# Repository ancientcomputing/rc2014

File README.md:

# RC2014
I consider Spencer Owen's RC2014 (http://rc2014.co.uk) the new S100 of the ancient computing era.
<p>
Spencer started off by designing a CPU and a family of modules around the ancient Zilog Z80 CPU. This is actually very similar to the original S100 bus design that was a derivative of the 8080 bus.
<p>
Since I'm a modder at heart, I've gone ahead and modified some of the Z80 software that originally came with the RC2014.
<p>
I have also developed a number of RC2014-compatible plug-in boards. These include a variety of memory and serial (UART) boards and more importantly, boards that allow the use of other CPUs like the <a href="https://en.wikipedia.org/wiki/Intel_8085">Intel 8085</a> and <a href="https://en.wikipedia.org/wiki/MOS_Technology_6502">6502</a> with the RC2014.
<p>
This repo holds my mods/additions and general contributions to the RC2014 community.
<p>
<hr>
<p>
<b>Software</b>
<p>
The source folder contains source code of projects related to the RC2014.
<p>
The 6502 sub-folder contains all the 6502-related source code including the Monitor/Debugger and Enhanced BASIC.
<p>
The Z80_8080 sub-folder contains all source code for Z80 and 8080 software including the Monitor/Debugger, MS BASIC, IMSAI 8K BASIC (for 8080) and various BIOS.
<p>
The original code that shipped with the RC2014 is at <a href="searle.hostei.com/grant">searle.hostei.com/grant</a>
<p>
The primary RC2014 Github repo is at: https://github.com/RC2014Z80/RC2014
<p>
<hr>
<p>
<b>ROM</b>
<p>
ROM images you can burn into EPROM/EEPROM for use with the RC2014 can be found in the ROM folder.
<p>
Not all combinations of CPU, serial, Monitor/Debugger, BASIC and ROM image sizes are available. When in doubt you can ask questions on the <a href="https://groups.google.com/forum/#!forum/rc2014-z80">RC2014 group</a> or <a href="http://forum.6502.org/">http://forum.6502.org/</a>.
<p>
<hr>
<p>
<b>RC2014 Add-on Modules</b>
<p>
The <b>eagle</b> folder contain a number of designs for add-on boards for the RC2014. The designs are in the form of Eagle files which can be used to order PCBs from manufacturers that can take .brd files. Or you can download the free version of Eagle and generate the necessary gerber files for your PCB vendor of choice.
<p>
Do also watch out for the OSH Park logos. Those are links to projects that I have shared on OSH Park, and you can order the boards directly from them. And no, I don't make a commission etc from your OSH Park orders.
<p>
For a full list of my shared projects, check out this <a href="https://oshpark.com/profiles/ancientcomputing">link</a>.
<p>
I have put some popular boards up for sale on <a href="https://www.tindie.com/stores/ancientcomputing/">Tindie</a>.
<p>
<hr>
<p>
Lastly, check out the documentation in the docs folder.
<p>
<hr>
<p>
Blog: http://ancientcomputing.blogspot.com

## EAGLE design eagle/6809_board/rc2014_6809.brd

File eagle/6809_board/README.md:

<b>6809 CPU Board for the RC2014</b>
<p>
These are the EAGLE files for the RC2014 6809 CPU Board.
<p>
The A15 line selects the inverted A15 signal from the 6809. This allows you to use the standard RC2014 memory and I/O boards by inverting the 2 halves of the memory space: ROM sits at top of memory and RAM at the bottom of memory.
<p>
The I/O space is decoded by the 74HCT688 and is mapped as a 256-byte block to the start of 0C000H. You will map the Z80 I/O addresses to the 6809 I/O space by adding 0C000H.
<p>
Compatibility:
<br>TBD
<p>
You can have boards made at OSH Park at the following link:
<p>
<a href="https://www.oshpark.com/shared_projects/m4Si7sne"></img></a>
<p>

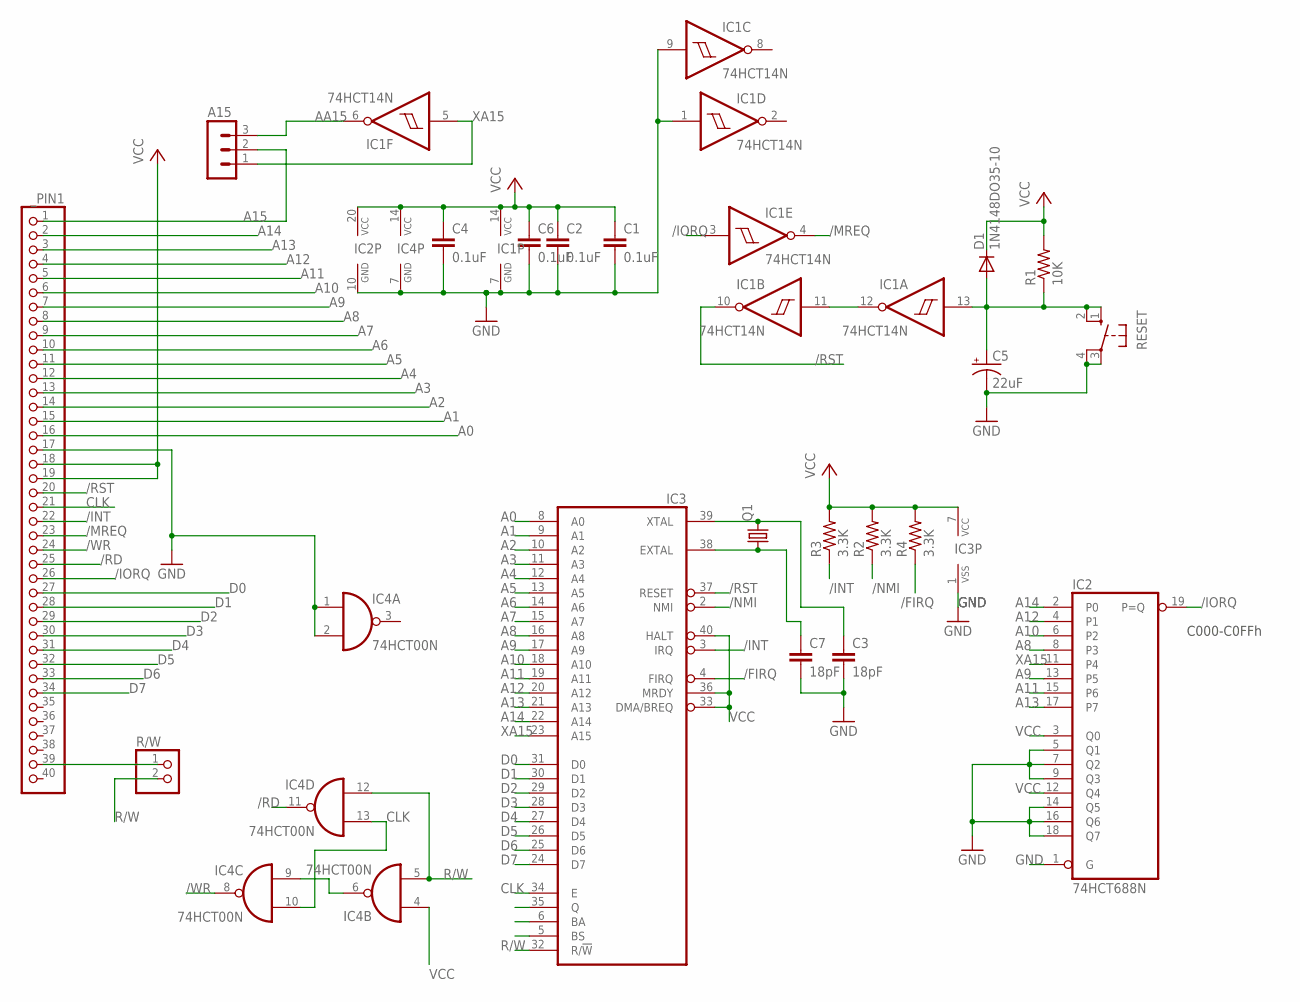
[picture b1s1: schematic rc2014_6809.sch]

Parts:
A15: MA03-1
C1, C2, C4, C6: 0.1uF; C050-024X044
C3, C7: 18pF; C050-024X044
C5: 22uF; TAP5-80
D1: 1N4148DO35-10; DO35-10
IC1: 74HCT14N; DIL14
IC2: 74HCT688N; DIL20
IC3: 6809; DIL40
IC4: 74HCT00N; DIL14
Q1: CRYSTALHC49S; HC49/S
R1: 10K; 0207/10
R2, R3, R4: 3.3K; 0207/10
R/W: PINHD-1X2; 1X02
RESET: 10-XX; B3F-10XX
_PIN1: PINHD-1X40; 1X40

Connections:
/FIRQ: IC3.4 (FIRQ), R4.1
/INT: IC3.3 (IRQ), R3.1, _PIN1.22
/IORQ: IC1.3 (I), IC2.19 (P=Q), _PIN1.26
/MREQ: IC1.4 (O), _PIN1.23
/NMI: IC3.2 (NMI), R2.1
/RD: IC4.11 (O), _PIN1.25
/RST: IC1.10 (O), IC3.37 (RESET), _PIN1.20
/WR: IC4.8 (O), _PIN1.24
A0: IC3.8 (A0), _PIN1.16
A1: IC3.9 (A1), _PIN1.15
A2: IC3.10 (A2), _PIN1.14
A3: IC3.11 (A3), _PIN1.13
A4: IC3.12 (A4), _PIN1.12
A5: IC3.13 (A5), _PIN1.11
A6: IC3.14 (A6), _PIN1.10
A7: IC3.15 (A7), _PIN1.9
A8: IC2.8 (P3), IC3.16 (A8), _PIN1.8
A9: IC2.13 (P5), IC3.17 (A9), _PIN1.7
A10: IC2.6 (P2), IC3.18 (A10), _PIN1.6
A11: IC2.15 (P6), IC3.19 (A11), _PIN1.5
A12: IC2.4 (P1), IC3.20 (A12), _PIN1.4
A13: IC2.17 (P7), IC3.21 (A13), _PIN1.3
A14: IC2.2 (P0), IC3.22 (A14), _PIN1.2
A15: A15.2, _PIN1.1
AA15: A15.3, IC1.6 (O)
CLK: IC3.34 (E), IC4.10 (I1), IC4.13 (I1), _PIN1.21
D0: IC3.31 (D0), _PIN1.27
D1: IC3.30 (D1), _PIN1.28
D2: IC3.29 (D2), _PIN1.29
D3: IC3.28 (D3), _PIN1.30
D4: IC3.27 (D4), _PIN1.31
D5: IC3.26 (D5), _PIN1.32
D6: IC3.25 (D6), _PIN1.33
D7: IC3.24 (D7), _PIN1.34
GND: C1.2, C2.2, C3.2, C4.2, C5.-, C6.2, C7.2, IC1.1 (I), IC1.7 (GND), IC1.9 (I), IC2.1 (G), IC2.5 (Q1), IC2.7 (Q2), IC2.9 (Q3), IC2.10 (GND), IC2.14 (Q5), IC2.16 (Q6), IC2.18 (Q7), IC3.1 (VSS), IC4.1 (I0), IC4.2 (I1), IC4.7 (GND), RESET.3, RESET.4 (P1), _PIN1.17
unnamed: IC4.6 (O), IC4.9 (I0)
unnamed: R/W.1, _PIN1.39
unnamed: IC1.11 (I), IC1.12 (O)
unnamed: C3.1, IC3.39 (XTAL), Q1.2
unnamed: C7.1, IC3.38 (EXTAL), Q1.1
R/W: IC3.32 (R/!W), IC4.5 (I1), IC4.12 (I0), R/W.2
RESET: C5.+, D1.A, IC1.13 (I), R1.1, RESET.1 (S), RESET.2 (S1)
VCC: C1.1, C2.1, C4.1, C6.1, D1.C, IC1.14 (VCC), IC2.3 (Q0), IC2.12 (Q4), IC2.20 (VCC), IC3.7 (VCC), IC3.33 (DMA/BREQ), IC3.36 (MRDY), IC3.40 (HALT), IC4.4 (I0), IC4.14 (VCC), R1.2, R2.2, R3.2, R4.2, _PIN1.18, _PIN1.19
XA15: A15.1, IC1.5 (I), IC2.11 (P4), IC3.23 (A15)

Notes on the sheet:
C000-C0FFh

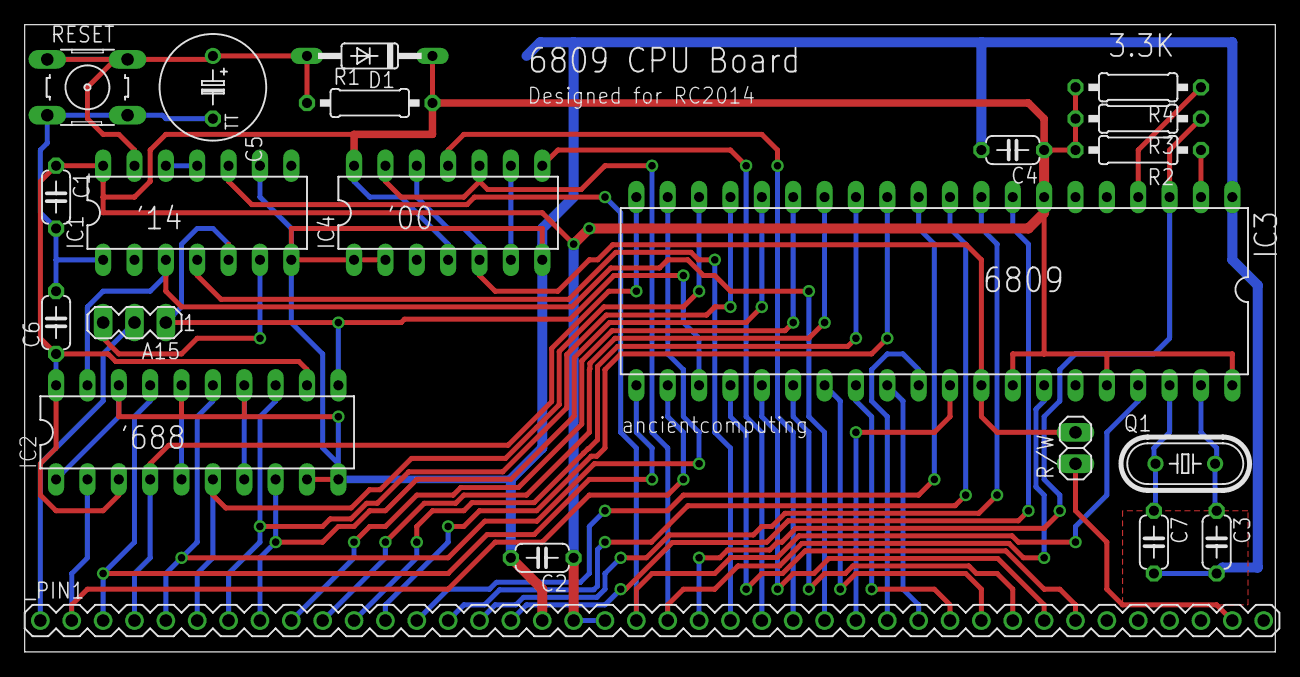
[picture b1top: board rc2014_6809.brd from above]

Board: 2 copper layers, 101.3 x 50.8 mm, 21 parts (0 on the bottom side), 44 nets.

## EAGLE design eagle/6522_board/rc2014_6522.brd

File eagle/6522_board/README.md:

<b>6522 VIA Board for the RC2014</b>
<p>
These are the Eagle files for the 6522 VIA Board for the RC2014.
<p>
The board is designed to work with the 6502 CPU Board.
<p>
If you have the initial revision (revA) of the 6502 CPU board, be sure to link a wire from the R/W signal of the 6502 to pin 39 of the RC2014 bus connector. The 6522 takes the R/W signal from that pin. RevB of the 6502 CPU board does not need that change but you want to make sure that the R/W jumper is closed.
<p>
Be sure to use a 6522 that is speed matched to the 6502 CPU.
<p>
Check out some test code <a href="https://github.com/ancientcomputing/rc2014/tree/master/source/6502/6522">here</a>.

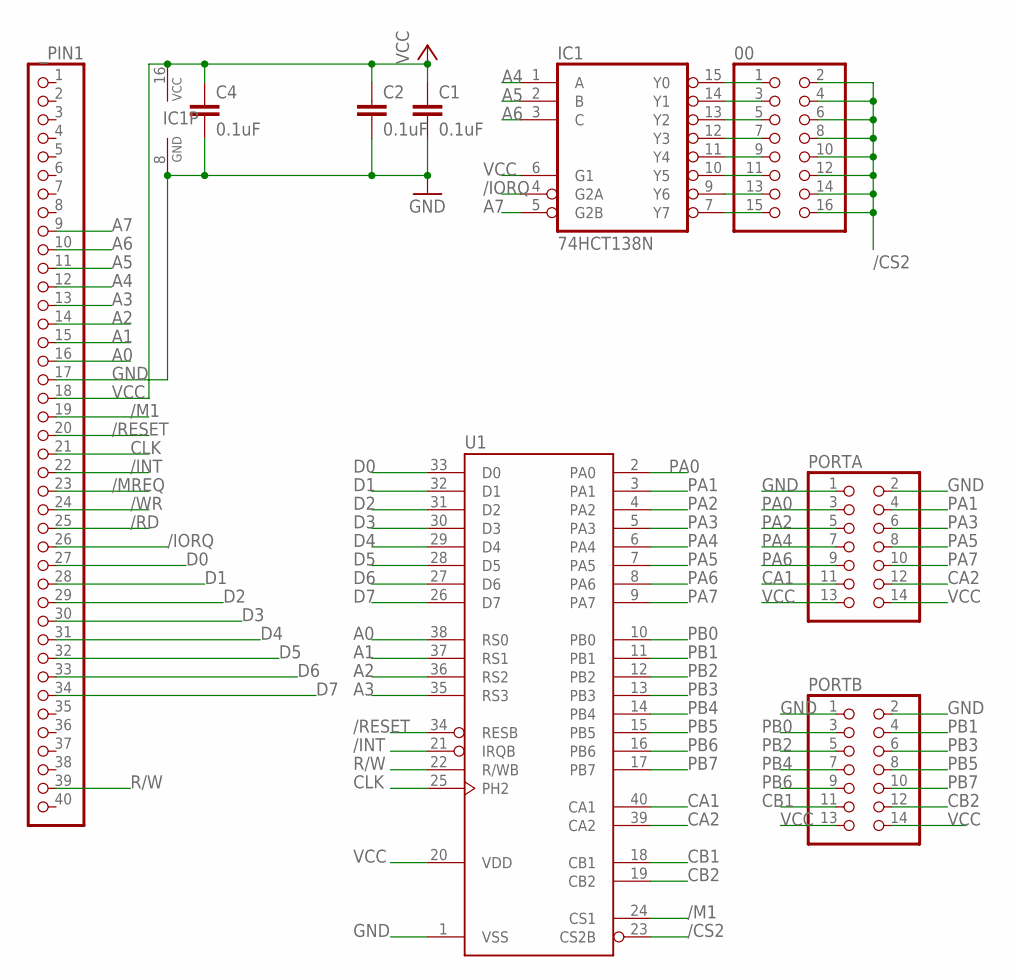
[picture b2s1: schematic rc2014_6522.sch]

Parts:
00: PINHD-2X8; 2X08
C1, C2, C4: 0.1uF; C050-024X044
IC1: 74HCT138N; DIL16
PORTA: PINHD-2X7; 2X07
PORTB: PINHD-2X7; 2X07
U1: G65SC22P; DIP-40
_PIN1: PINHD-1X40; 1X40

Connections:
/CS2: 00.2, 00.4, 00.6, 00.8, 00.10, 00.12, 00.14, 00.16, U1.23 (CS2B)
/INT: U1.21 (IRQB), _PIN1.22
/IORQ: IC1.4 (G2A), _PIN1.26
/M1: U1.24 (CS1), _PIN1.19
/MREQ: _PIN1.23
/RD: _PIN1.25
/RESET: U1.34 (RESB), _PIN1.20
/WR: _PIN1.24
A0: U1.38 (RS0), _PIN1.16
A1: U1.37 (RS1), _PIN1.15
A2: U1.36 (RS2), _PIN1.14
A3: U1.35 (RS3), _PIN1.13
A4: IC1.1 (A), _PIN1.12
A5: IC1.2 (B), _PIN1.11
A6: IC1.3 (C), _PIN1.10
A7: IC1.5 (G2B), _PIN1.9
CA1: PORTA.11, U1.40 (CA1)
CA2: PORTA.12, U1.39 (CA2)
CB1: PORTB.11, U1.18 (CB1)
CB2: PORTB.12, U1.19 (CB2)
CLK: U1.25 (PH2), _PIN1.21
D0: U1.33 (D0), _PIN1.27
D1: U1.32 (D1), _PIN1.28
D2: U1.31 (D2), _PIN1.29
D3: U1.30 (D3), _PIN1.30
D4: U1.29 (D4), _PIN1.31
D5: U1.28 (D5), _PIN1.32
D6: U1.27 (D6), _PIN1.33
D7: U1.26 (D7), _PIN1.34
GND: C1.2, C2.2, C4.2, IC1.8 (GND), PORTA.1, PORTA.2, PORTB.1, PORTB.2, U1.1 (VSS), _PIN1.17
unnamed: 00.1, IC1.15 (Y0)
unnamed: 00.3, IC1.14 (Y1)
unnamed: 00.5, IC1.13 (Y2)
unnamed: 00.7, IC1.12 (Y3)
unnamed: 00.9, IC1.11 (Y4)
unnamed: 00.11, IC1.10 (Y5)
unnamed: 00.13, IC1.9 (Y6)
unnamed: 00.15, IC1.7 (Y7)
PA0: PORTA.3, U1.2 (PA0)
PA1: PORTA.4, U1.3 (PA1)
PA2: PORTA.5, U1.4 (PA2)
PA3: PORTA.6, U1.5 (PA3)
PA4: PORTA.7, U1.6 (PA4)
PA5: PORTA.8, U1.7 (PA5)
PA6: PORTA.9, U1.8 (PA6)
PA7: PORTA.10, U1.9 (PA7)
PB0: PORTB.3, U1.10 (PB0)
PB1: PORTB.4, U1.11 (PB1)
PB2: PORTB.5, U1.12 (PB2)
PB3: PORTB.6, U1.13 (PB3)
PB4: PORTB.7, U1.14 (PB4)
PB5: PORTB.8, U1.15 (PB5)
PB6: PORTB.9, U1.16 (PB6)
PB7: PORTB.10, U1.17 (PB7)
R/W: U1.22 (R/WB), _PIN1.39
VCC: C1.1, C2.1, C4.1, IC1.6 (G1), IC1.16 (VCC), PORTA.13, PORTA.14, PORTB.13, PORTB.14, U1.20 (VDD), _PIN1.18

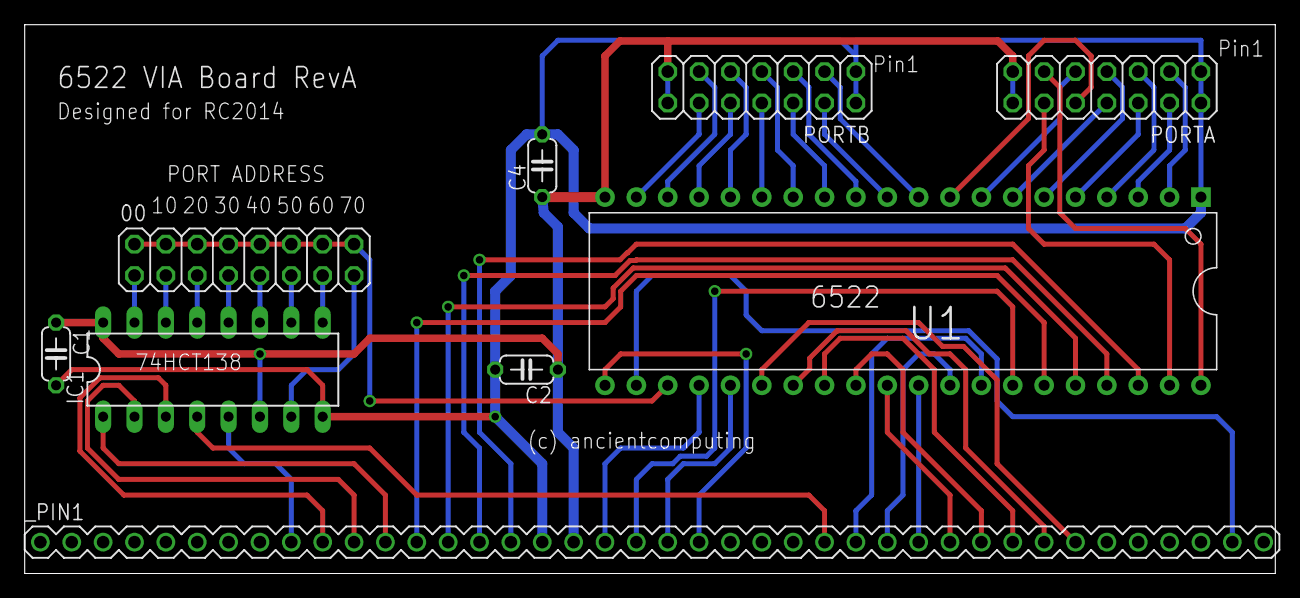
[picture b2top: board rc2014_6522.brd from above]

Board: 2 copper layers, 101.3 x 44.4 mm, 9 parts (0 on the bottom side), 53 nets.

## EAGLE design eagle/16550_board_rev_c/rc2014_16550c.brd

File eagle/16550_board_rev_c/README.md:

<b>16550 UART Board for RC2014</b>
<p>
This is RevC of the 16550 UART Board, designed for RC2014 systems.
<p>
Unlike earlier versions, this board takes the PLCC version of the 16550. I have successfully tested it with a TL16C550CFN from Mouser (part: 595-TL16C550CFN).
<p>
Also, as you can see from the Mouser part number, PLCC versions of the 16C550 are still commercially available. The DIP/DIL-40 versions are no longer so.
<p>
The use of a 16C550 in a 6502 system is important (vs the 16550 version) because the 6502 BIOS enables autoflow control. This provides a means of throttling the byte stream from your PC when you are uploading an Intel Hex file.
<p>
The other major change is the use of a 74HCT138 to give you more addressing options. This allows you to use more than one board in a system: you just need to make sure that each board uses a different port address. Of course, the software needs to be appropriately modified to access port addresses other than C0H which is the default one.
<p>
Finally, the PLCC socket is a standard part and can be ordered from Mouser (part: 806-PX-44LCC) or Jameco.
<p>
You can have boards made at OSH Park:<br>
<a href="https://www.oshpark.com/shared_projects/Rv3GdG3o"></img></a>
<p> 
Or order them on <a href="https://www.tindie.com/products/9981/">Tindie</a>.

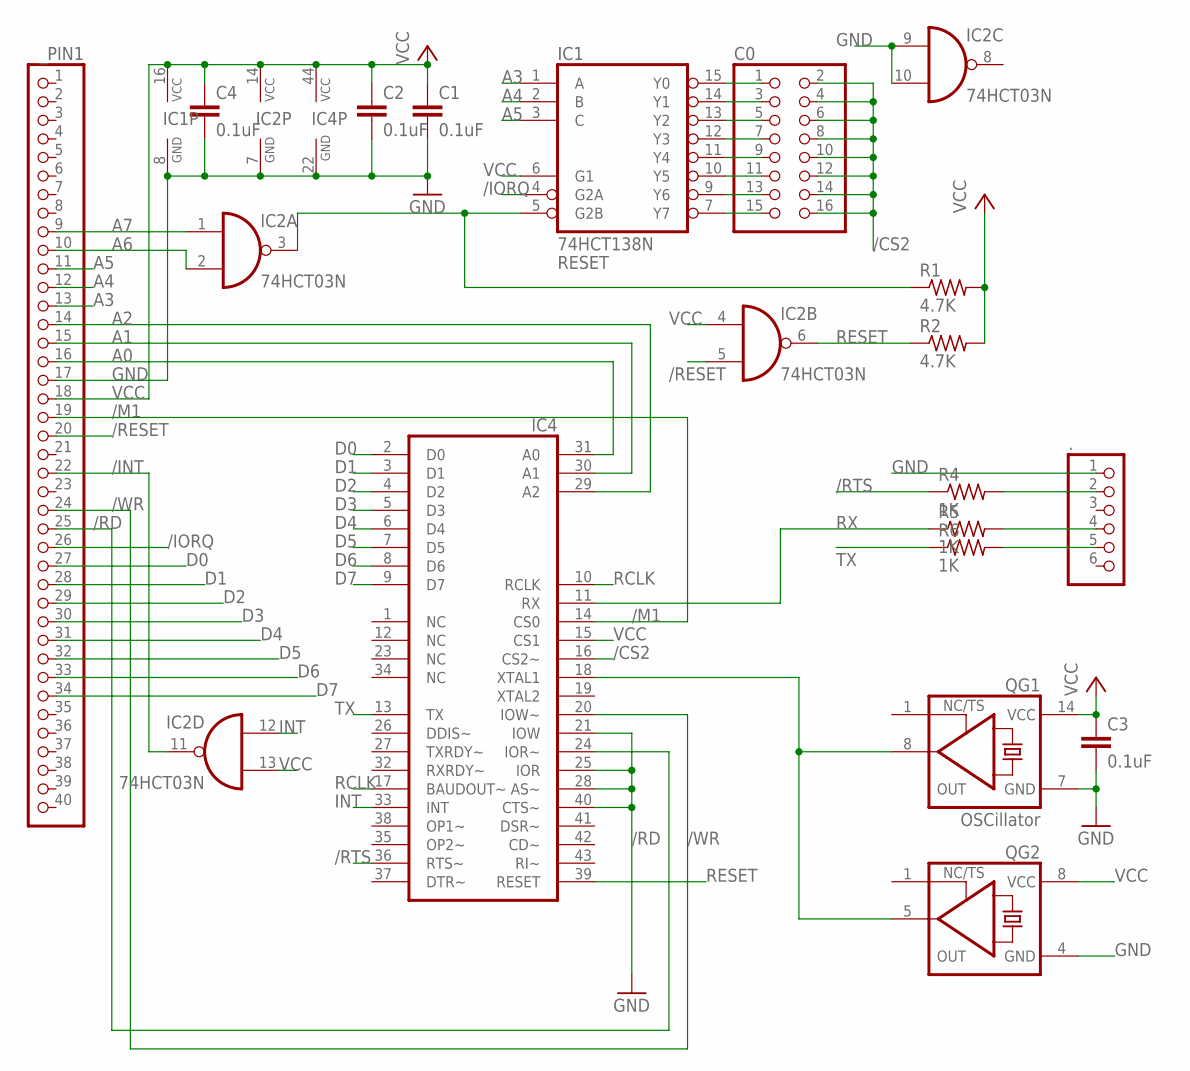
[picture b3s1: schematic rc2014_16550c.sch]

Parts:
.: PINHD-1X6; 1X06
C0: PINHD-2X8; 2X08
C1, C2, C3, C4: 0.1uF; C050-024X044
IC1: 74HCT138N; DIL16
IC2: 74HCT03N; DIL14
IC4: XR-16C550JSOCKET44; S44
QG1: OSCillator; DIL14S
QG2: XO-8; DIL08S
R1, R2: 4.7K; 0207/10
R4, R5, R6: 1K; 0207/10
_PIN1: PINHD-1X40; 1X40

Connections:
/CS2: C0.2, C0.4, C0.6, C0.8, C0.10, C0.12, C0.14, C0.16, IC4.16 (CS2~)
/INT: IC2.11 (O), _PIN1.22
/IORQ: IC1.4 (G2A), _PIN1.26
/M1: IC4.14 (CS0), _PIN1.19
/RD: IC4.24 (IOR~), _PIN1.25
/RESET: IC2.5 (I1), _PIN1.20
/RTS: IC4.36 (RTS~), R4.1
/WR: IC4.20 (IOW~), _PIN1.24
A0: IC4.31 (A0), _PIN1.16
A1: IC4.30 (A1), _PIN1.15
A2: IC4.29 (A2), _PIN1.14
A3: IC1.1 (A), _PIN1.13
A4: IC1.2 (B), _PIN1.12
A5: IC1.3 (C), _PIN1.11
A6: IC2.2 (I1), _PIN1.10
A7: IC2.1 (I0), _PIN1.9
CS1: IC1.5 (G2B), IC2.3 (O), R1.1
D0: IC4.2 (D0), _PIN1.27
D1: IC4.3 (D1), _PIN1.28
D2: IC4.4 (D2), _PIN1.29
D3: IC4.5 (D3), _PIN1.30
D4: IC4.6 (D4), _PIN1.31
D5: IC4.7 (D5), _PIN1.32
D6: IC4.8 (D6), _PIN1.33
D7: IC4.9 (D7), _PIN1.34
GND: ..1, C1.2, C2.2, C3.2, C4.2, IC1.8 (GND), IC2.7 (GND), IC2.9 (I0), IC2.10 (I1), IC4.21 (IOW), IC4.22 (GND), IC4.25 (IOR), IC4.28 (AS~), IC4.40 (CTS~), QG1.7 (GND), QG2.4 (GND), _PIN1.17
INT: IC2.12 (I0), IC4.33 (INT)
unnamed: ..5, R6.2
unnamed: ..4, R5.2
unnamed: ..2, R4.2
unnamed: C0.1, IC1.15 (Y0)
unnamed: C0.3, IC1.14 (Y1)
unnamed: C0.5, IC1.13 (Y2)
unnamed: C0.7, IC1.12 (Y3)
unnamed: C0.9, IC1.11 (Y4)
unnamed: C0.11, IC1.10 (Y5)
unnamed: C0.13, IC1.9 (Y6)
unnamed: C0.15, IC1.7 (Y7)
OSC: IC4.18 (XTAL1), QG1.8 (OUT), QG2.5 (OUT)
RCLK: IC4.10 (RCLK), IC4.17 (BAUDOUT~)
RESET: IC2.6 (O), IC4.39 (RESET), R2.1
RX: IC4.11 (RX), R5.1
TX: IC4.13 (TX), R6.1
VCC: C1.1, C2.1, C3.1, C4.1, IC1.6 (G1), IC1.16 (VCC), IC2.4 (I0), IC2.13 (I1), IC2.14 (VCC), IC4.15 (CS1), IC4.44 (VCC), QG1.14 (VCC), QG2.8 (VCC), R1.2, R2.2, _PIN1.18

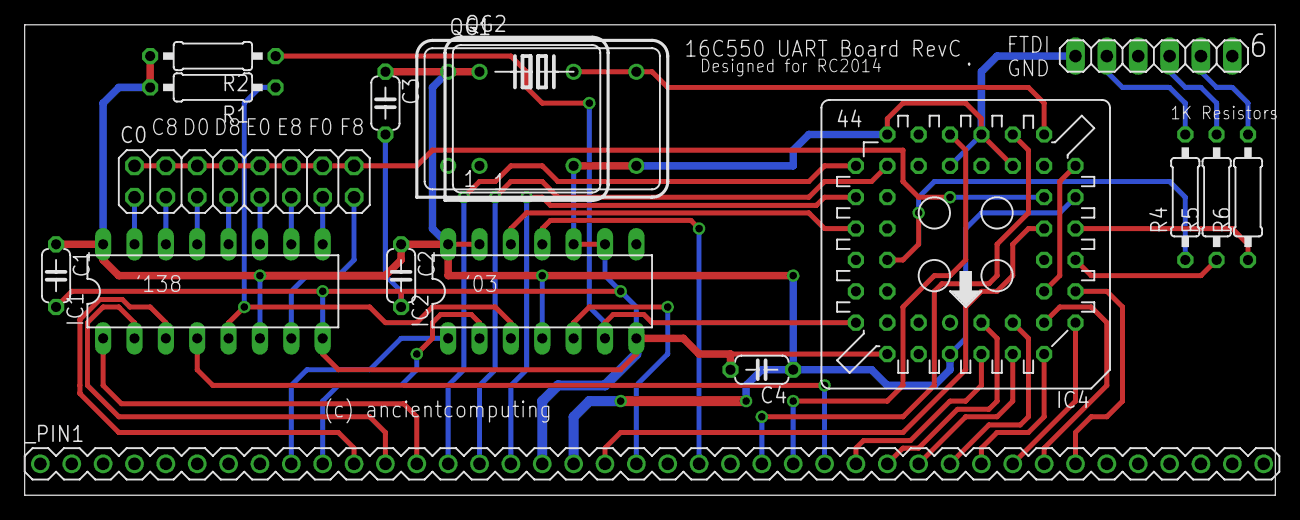
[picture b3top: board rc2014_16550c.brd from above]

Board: 2 copper layers, 101.3 x 38.1 mm, 17 parts (0 on the bottom side), 44 nets.

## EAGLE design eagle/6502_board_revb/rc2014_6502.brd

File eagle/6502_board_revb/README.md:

<b>6502 CPU Board for the RC2014 RevB</b>
<p>
This is the RevB version of the board.
<p>
New:
<br>
- Optional jumper to connect R/W to pin 39 of the bus
<br>
- A14 can be inverted. Inverting A14 will allow you to use the RC2014 64KB RAM board. Configure that board for 48KB of RAM, starting from 4000h. The inverted A14 will map the 48KB to 0-BFFFh in the 6502 address space, giving you a whopping 48KB of RAM!
<br>
- NMI can be accessed with a test pin/point
<br>
- You can use a 1/2 size oscillator.
<p>
Otherwise this board works the same as the original version.
<p>
You can have boards made at OSH Park at the following link:
<br>
<a href="https://www.oshpark.com/shared_projects/QY9iHV77"></img></a>
<p>
Otherwise, you can order boards on <a href="https://www.tindie.com/products/9916/">Tindie</a>.

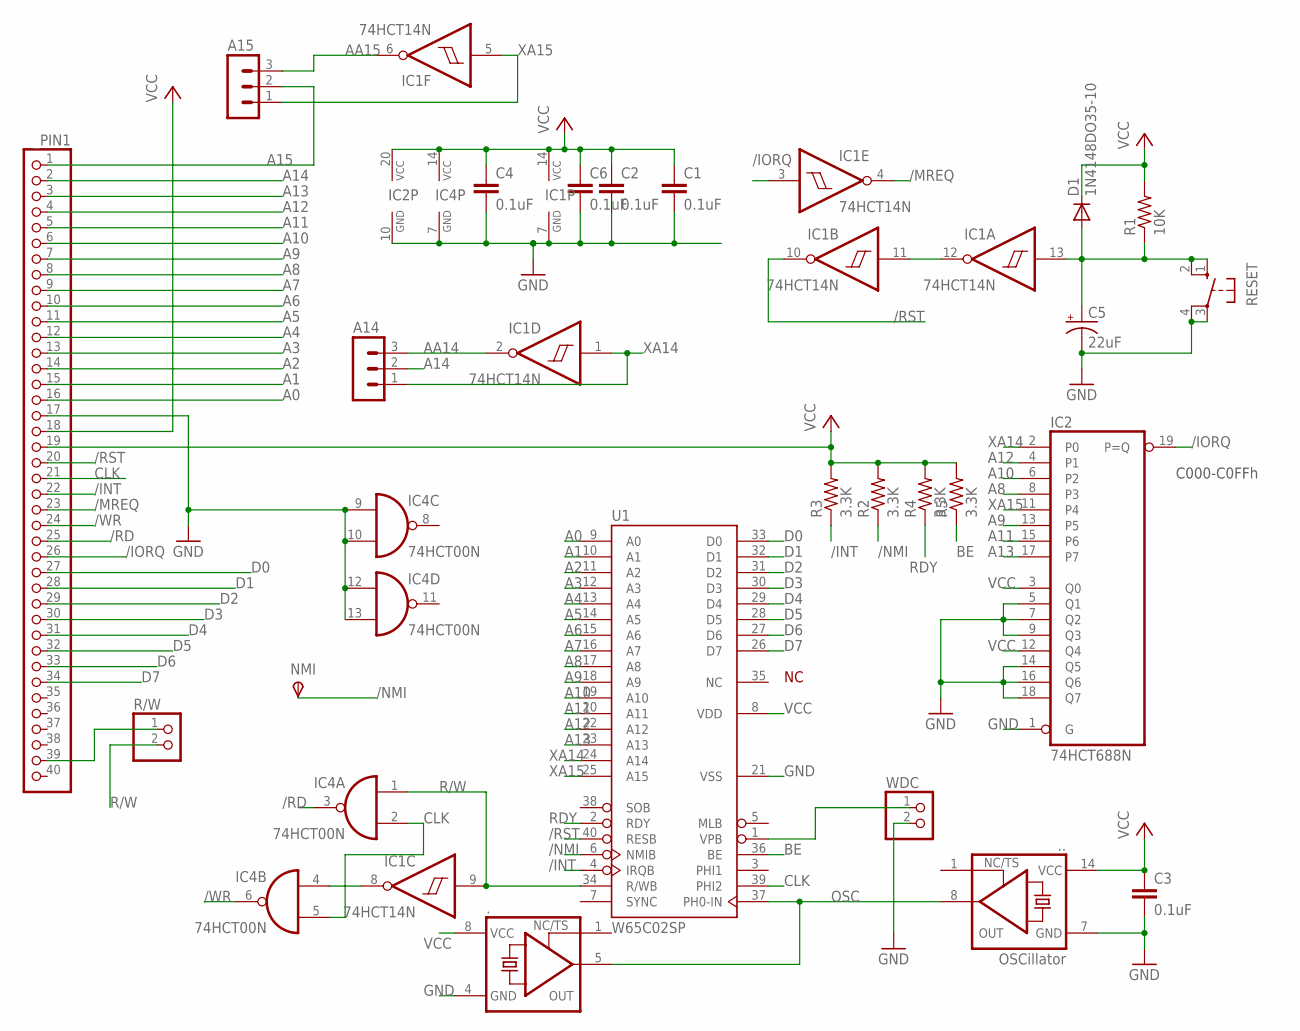
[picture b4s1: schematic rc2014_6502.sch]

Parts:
.: XO-8; DIL08S
..: OSCillator; DIL14S
A14, A15: MA03-1
C1, C2, C3, C4, C6: 0.1uF; C050-024X044
C5: 22uF; TAP5-80
D1: 1N4148DO35-10; DO35-10
IC1: 74HCT14N; DIL14
IC2: 74HCT688N; DIL20
IC4: 74HCT00N; DIL14
NMI: TPSPAD1-13; P1-13
R1: 10K; 0207/10
R2, R3, R4, R5: 3.3K; 0207/10
R/W: PINHD-1X2; 1X02
RESET: 10-XX; B3F-10XX
U1: W65C02SP; DIP-40
WDC: PINHD-1X2; 1X02
_PIN1: PINHD-1X40; 1X40

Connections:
/INT: R3.1, U1.4 (IRQB), _PIN1.22
/IORQ: IC1.3 (I), IC2.19 (P=Q), _PIN1.26
/MREQ: IC1.4 (O), _PIN1.23
/NMI: NMI.TP, R2.1, U1.6 (NMIB)
/RD: IC4.3 (O), _PIN1.25
/RST: IC1.10 (O), U1.40 (RESB), _PIN1.20
/WR: IC4.6 (O), _PIN1.24
A0: U1.9 (A0), _PIN1.16
A1: U1.10 (A1), _PIN1.15
A2: U1.11 (A2), _PIN1.14
A3: U1.12 (A3), _PIN1.13
A4: U1.13 (A4), _PIN1.12
A5: U1.14 (A5), _PIN1.11
A6: U1.15 (A6), _PIN1.10
A7: U1.16 (A7), _PIN1.9
A8: IC2.8 (P3), U1.17 (A8), _PIN1.8
A9: IC2.13 (P5), U1.18 (A9), _PIN1.7
A10: IC2.6 (P2), U1.19 (A10), _PIN1.6
A11: IC2.15 (P6), U1.20 (A11), _PIN1.5
A12: IC2.4 (P1), U1.22 (A12), _PIN1.4
A13: IC2.17 (P7), U1.23 (A13), _PIN1.3
A14: A14.2, _PIN1.2
A15: A15.2, _PIN1.1
AA14: A14.3, IC1.2 (O)
AA15: A15.3, IC1.6 (O)
BE: R5.1, U1.36 (BE)
CLK: IC4.2 (I1), IC4.5 (I1), U1.39 (PHI2), _PIN1.21
D0: U1.33 (D0), _PIN1.27
D1: U1.32 (D1), _PIN1.28
D2: U1.31 (D2), _PIN1.29
D3: U1.30 (D3), _PIN1.30
D4: U1.29 (D4), _PIN1.31
D5: U1.28 (D5), _PIN1.32
D6: U1.27 (D6), _PIN1.33
D7: U1.26 (D7), _PIN1.34
GND: ..4 (GND), ...7 (GND), C1.2, C2.2, C3.2, C4.2, C5.-, C6.2, IC1.7 (GND), IC2.1 (G), IC2.5 (Q1), IC2.7 (Q2), IC2.9 (Q3), IC2.10 (GND), IC2.14 (Q5), IC2.16 (Q6), IC2.18 (Q7), IC4.7 (GND), IC4.9 (I0), IC4.10 (I1), IC4.12 (I0), IC4.13 (I1), RESET.3, RESET.4 (P1), U1.21 (VSS), WDC.2, _PIN1.17
unnamed: IC1.8 (O), IC4.4 (I0)
unnamed: R/W.1, _PIN1.39
unnamed: U1.1 (VPB), WDC.1
unnamed: IC1.11 (I), IC1.12 (O)
OSC: ..5 (OUT), ...8 (OUT), U1.37 (PH0-IN)
R/W: IC1.9 (I), IC4.1 (I0), R/W.2, U1.34 (R/WB)
RDY: R4.1, U1.2 (RDY)
RESET: C5.+, D1.A, IC1.13 (I), R1.1, RESET.1 (S), RESET.2 (S1)
VCC: ..8 (VCC), ...14 (VCC), C1.1, C2.1, C3.1, C4.1, C6.1, D1.C, IC1.14 (VCC), IC2.3 (Q0), IC2.12 (Q4), IC2.20 (VCC), IC4.14 (VCC), R1.2, R2.2, R3.2, R4.2, R5.2, U1.8 (VDD), _PIN1.18, _PIN1.19
XA14: A14.1, IC1.1 (I), IC2.2 (P0), U1.24 (A14)
XA15: A15.1, IC1.5 (I), IC2.11 (P4), U1.25 (A15)

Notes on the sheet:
C000-C0FFh

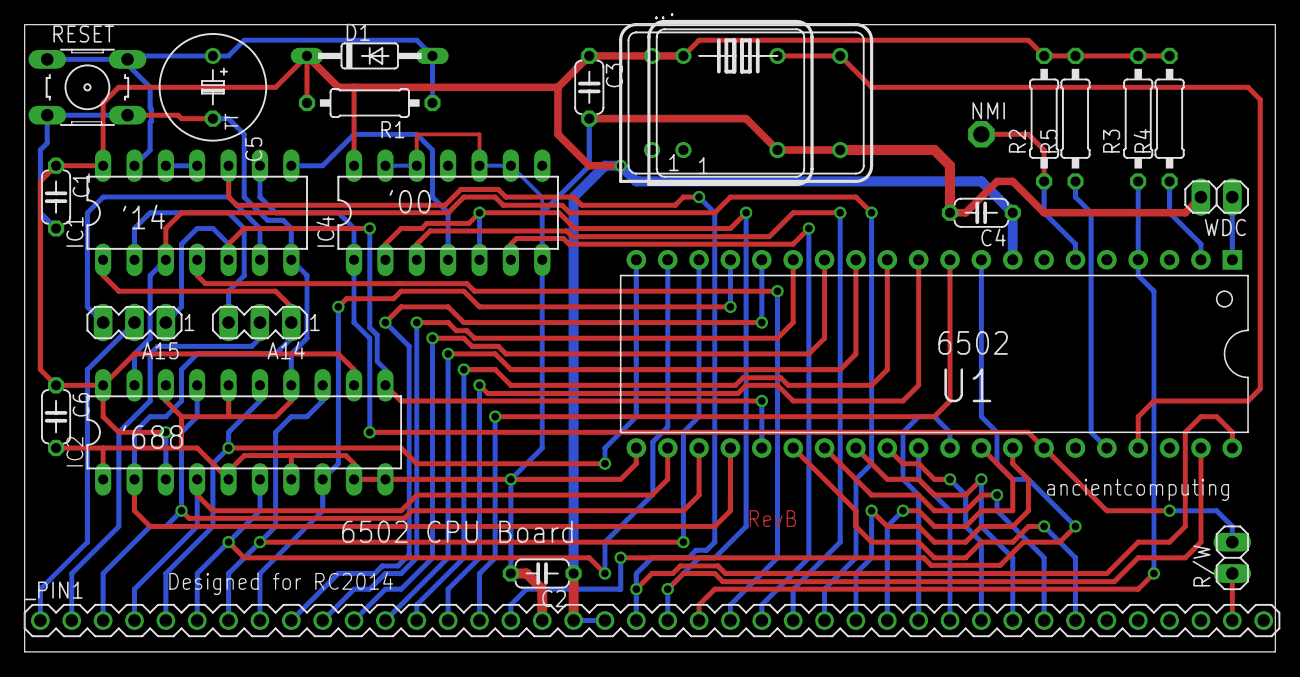
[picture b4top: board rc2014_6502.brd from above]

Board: 2 copper layers, 101.3 x 50.8 mm, 25 parts (0 on the bottom side), 47 nets.

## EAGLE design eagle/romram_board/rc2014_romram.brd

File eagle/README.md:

<b>Eagle files for RC2014 add-on boards</b>
<p>
<b>16550 board (TESTED)</b>: Simple board for 16550, 16C550 and similar UART devices. Can be used with 1.8432MHz or 7.3728MHz oscillators. Note that pin 1 (GND) of the FTDI connector is on the left (looking at the board with the bus connector at the bottom).
<p>
The port address starts at 80H. A new BIOS is available. See source/16x550. Binaries are at rom/16x550.
<p>
There is no option to power the system from the FTDI header.
<p>
<b>16550 board Rev B (TESTED)</b>: A variant of the 16550 board implementation. Using 74HCT03 open collector gates, particularly to drive the /INT line. This means that other peripherals can also drive the /INT line. 
<p>
The port address starts at C0H. A new BIOS will be made available for this. For the impatient, just change the uart_base value to 0c0h from 80h.
<p>
<b>16550 board Rev C (TESTED)</b>: Yet another variant of the 16550 board implementation. This time, it uses the PLCC version of the 16550 which is still a current part. This board is also compatible with the new 16C750 which has 64-character FIFOs!
<p>
<b>z80_board (TESTED)</b>: This is an opinionated implementation of a CPU module for the RC2014. It is designed for the v1.0 bus but may work for the Pro/v2 bus. The opinionated parts of the design is a bona fide reset circuit (the firmware should start up on power up), and the use of a crystal oscillator.
<p>
The crystal oscillator can be connected to the RC2014 bus or not. The decoupling of the Z80's clock from the bus clock means that you are no longer bounded by the requirements of the UART baudrate. You will be able to run the Z80 at 20MHz (assuming you have the 20MHz part and that the bus doesn't impact the high frequency signals too much).
<p>
This Z80 board is compatible with other RC2014 modules. If you plan to use this with the 68B50 ACIA module, you will have to use a 7.3728MHz oscillator and short the CLOCK jumper.
<p>
<b>8085_board (TESTED)</b>: Use another CPU with the RC2014! The 8085 is the step-sibling of the Z80. This implementation exposes the SID/SOD lines to an FTDI header so that you can run with a serial terminal without the use of a UART card. A 6.144MHz crystal is recommended for compatibility with the Tiny Basic found <a href="https://github.com/ancientcomputing/8080_8085/tree/master/Tiny_Basic">here</a>.
<p>
A Monitor can also be found in the <a href="https://github.com/ancientcomputing/rc2014/tree/master/rom/8080_8085/monitor/">8085 folder</a>.
<p>
<b>Real Retro 3KB RAM board aka rr3kram (TESTED)</b>: Remember when 3KB was a lot of memory? The Real Retro 3KB RAM board tries to relive that experience. It uses 3 pairs of 2114 RAM chips to deliver a massive 3KB of memory.
<p>
With 200ns devices, it will even work with the Z80 CPU+ board equiped with a blistering fast 14MHz Z80.
<p>
The original board design had disconnected A0, A1 lines which have now been fixed.   
<p>
<b>Real Retro UART board (TESTED)</b>
<p>
A basic UART board using ancient UART devices like the 6402, AY-3-1015 or similar.
<p>
<b>Simple ROM/RAM board (TESTED)</b>
<p>
A simple board providing 32KB of RAM and 32KB of ROM. Usable with EPROM or EEPROM. Switchable to allow ROM at the top of memory or at the bottom of memory. This provides for compatibility with 6502 or 680x CPU boards.
<p>
<b>6502 CPU Board (TESTED)</b>
<p>
Run the 6502 microprocessor on the RC2014!
<p>
The 6502, along with the Z80, powered much of the home computer industry in the late 1970s and 1980s.
<p>
My blog <a href="https://ancientcomputing.blogspot.com">ancientcomputing.blogspot.com</a> has a number of articles that cover how the 6502 bus was made to work on the RC2014 bus and which RC2014 boards can work (with or without minor modifications) with the 6502 CPU board.
<p>
<b>6502 CPU Board RevB (TESTED)</b>
<p>
The RevB version of the 6502 CPU board gives you the option of inverting the A14 address line as well. You can use it with the RC2014 64KB RAM card to build a system with 48KB of usable RAM.
<p>
<b>6522 VIA Board (TESTED)</b>
<p>
You can start building up a 6502-based RC2014 system using native 6502 peripherals starting with the 6522 VIA board.
<p>
<hr>
<p>
<b>IMPORTANT</b>: These designs unless described otherwise are at the prototype stage as of now. I have put in the initial board orders at OSH Park and have not tested any of the designs. If you do find errors, please flag them!
<p>
kicadis are encouraged to convert the files to kicad format with the sole requirement that the converted files are made freely available aka "open source"...
<p>
Copyright Ben Chong and freely licensed back to the community.
<p>
<hr>
<p>

<p>

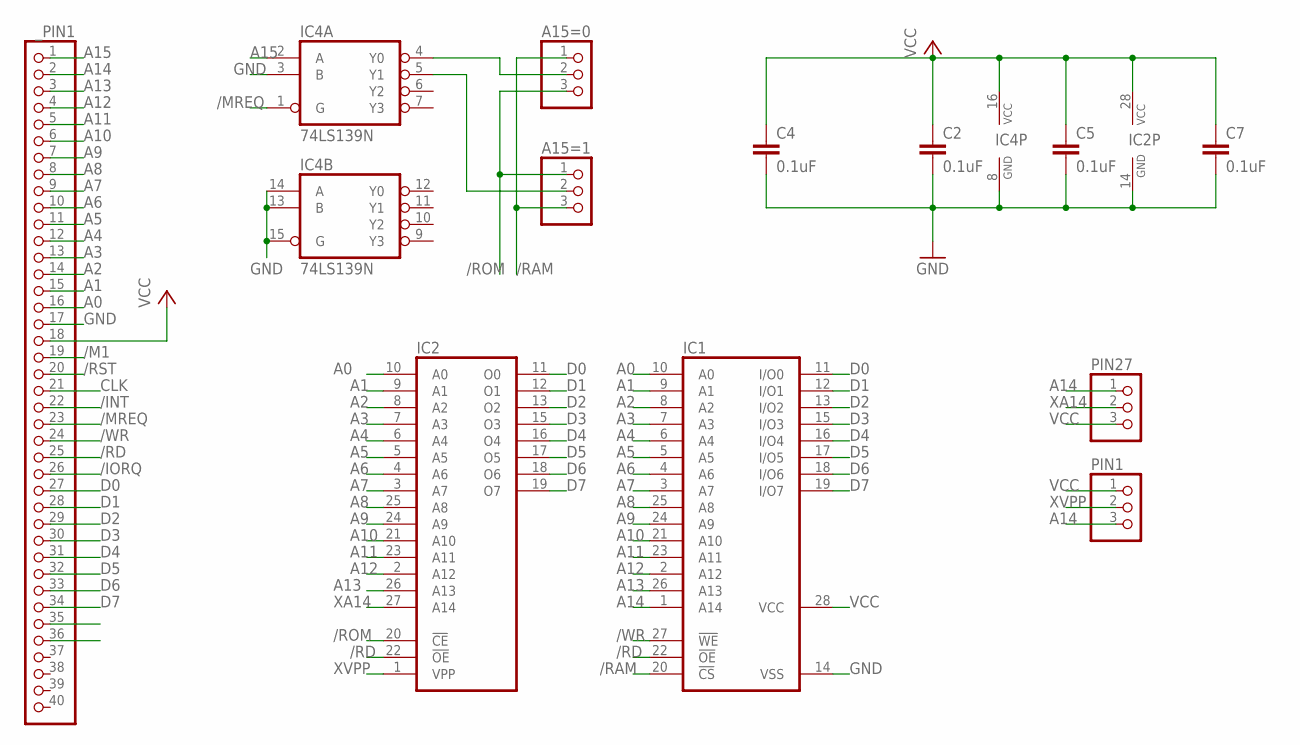
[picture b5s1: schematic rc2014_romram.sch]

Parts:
A15=0, A15=1: PINHD-1X3; 1X03
C2, C4, C5, C7: 0.1uF; C050-024X044
IC1: 62256P; DIL28-6
IC2: 27256; DIL28
IC4: 74LS139N; DIL16
PIN1, PIN27: PINHD-1X3; 1X03
_PIN1: PINHD-1X40; 1X40

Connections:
/INT: _PIN1.22
/IORQ: _PIN1.26
/M1: _PIN1.19
/MREQ: IC4.1 (G), _PIN1.23
/RAM: A15=0.1, A15=1.3, IC1.20 (!CS)
/RD: IC1.22 (!OE), IC2.22 (!OE), _PIN1.25
/ROM: A15=0.3, A15=1.1, IC2.20 (!CE)
/RST: _PIN1.20
/WR: IC1.27 (!WE), _PIN1.24
A0: IC1.10 (A0), IC2.10 (A0), _PIN1.16
A1: IC1.9 (A1), IC2.9 (A1), _PIN1.15
A2: IC1.8 (A2), IC2.8 (A2), _PIN1.14
A3: IC1.7 (A3), IC2.7 (A3), _PIN1.13
A4: IC1.6 (A4), IC2.6 (A4), _PIN1.12
A5: IC1.5 (A5), IC2.5 (A5), _PIN1.11
A6: IC1.4 (A6), IC2.4 (A6), _PIN1.10
A7: IC1.3 (A7), IC2.3 (A7), _PIN1.9
A8: IC1.25 (A8), IC2.25 (A8), _PIN1.8
A9: IC1.24 (A9), IC2.24 (A9), _PIN1.7
A10: IC1.21 (A10), IC2.21 (A10), _PIN1.6
A11: IC1.23 (A11), IC2.23 (A11), _PIN1.5
A12: IC1.2 (A12), IC2.2 (A12), _PIN1.4
A13: IC1.26 (A13), IC2.26 (A13), _PIN1.3
A14: IC1.1 (A14), PIN1.3, PIN27.1, _PIN1.2
A15: IC4.2 (A), _PIN1.1
CLK: _PIN1.21
D0: IC1.11 (I/O0), IC2.11 (O0), _PIN1.27
D1: IC1.12 (I/O1), IC2.12 (O1), _PIN1.28
D2: IC1.13 (I/O2), IC2.13 (O2), _PIN1.29
D3: IC1.15 (I/O3), IC2.15 (O3), _PIN1.30
D4: IC1.16 (I/O4), IC2.16 (O4), _PIN1.31
D5: IC1.17 (I/O5), IC2.17 (O5), _PIN1.32
D6: IC1.18 (I/O6), IC2.18 (O6), _PIN1.33
D7: IC1.19 (I/O7), IC2.19 (O7), _PIN1.34
GND: C2.2, C4.2, C5.2, C7.2, IC1.14 (VSS), IC2.14 (GND), IC4.3 (B), IC4.8 (GND), IC4.13 (B), IC4.14 (A), IC4.15 (G), _PIN1.17
unnamed: A15=0.2, IC4.4 (Y0)
unnamed: A15=1.2, IC4.5 (Y1)
VCC: C2.1, C4.1, C5.1, C7.1, IC1.28 (VCC), IC2.28 (VCC), IC4.16 (VCC), PIN1.1, PIN27.3, _PIN1.18
XA14: IC2.27 (A14), PIN27.2
XVPP: IC2.1 (VPP), PIN1.2

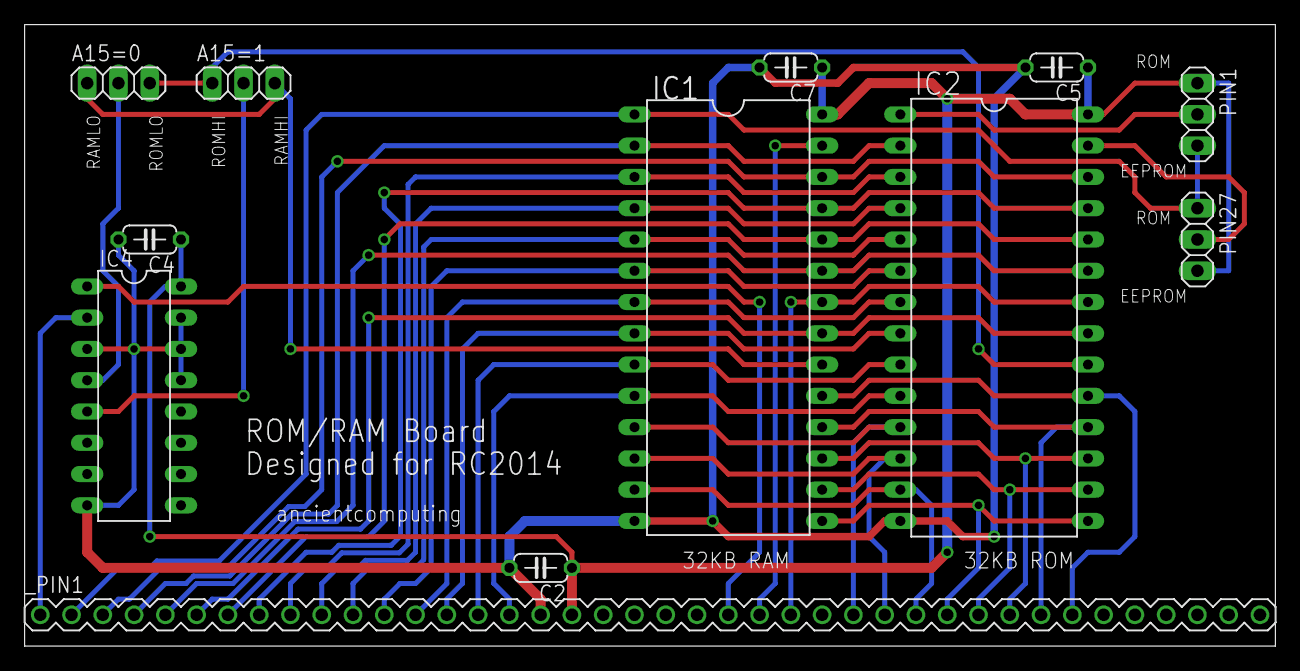
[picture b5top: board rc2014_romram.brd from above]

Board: 2 copper layers, 101.6 x 50.5 mm, 12 parts (0 on the bottom side), 35 nets.

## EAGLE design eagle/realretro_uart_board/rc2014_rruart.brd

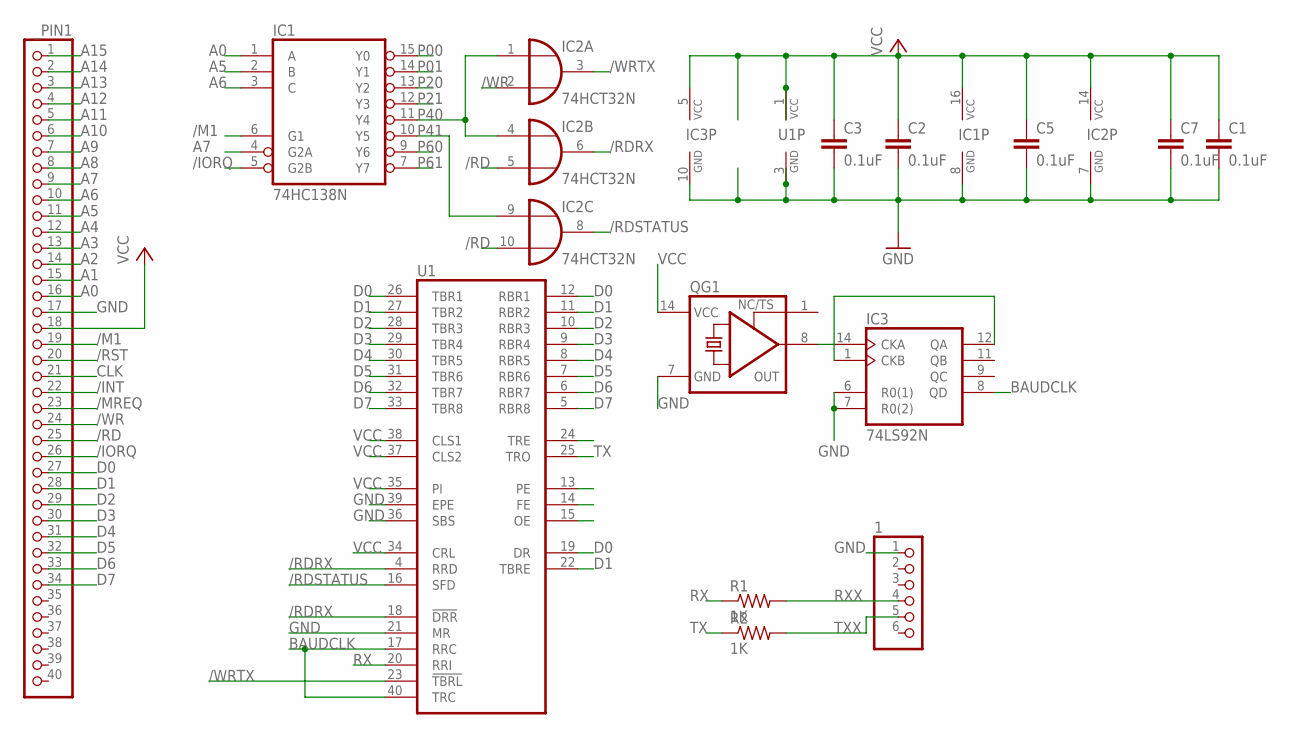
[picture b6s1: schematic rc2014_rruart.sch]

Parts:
1: PINHD-1X6; 1X06
C1, C2, C3, C5, C7: 0.1uF; C050-024X044
IC1: 74HC138N; DIL16
IC2: 74HCT32N; DIL14
IC3: 74LS92N; DIL14
QG1: XO-14; DIL14S
R1, R2: 1K; 0207/10
U1: HD6402; DIL40
_PIN1: PINHD-1X40; 1X40

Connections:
/INT: _PIN1.22
/IORQ: IC1.5 (G2B), _PIN1.26
/M1: IC1.6 (G1), _PIN1.19
/MREQ: _PIN1.23
/RD: IC2.5 (I1), IC2.10 (I1), _PIN1.25
/RDRX: IC2.6 (O), U1.4 (RRD), U1.18 (!DRR)
/RDSTATUS: IC2.8 (O), U1.16 (SFD)
/RST: _PIN1.20
/WR: IC2.2 (I1), _PIN1.24
/WRTX: IC2.3 (O), U1.23 (!TBRL)
A0: IC1.1 (A), _PIN1.16
A1: _PIN1.15
A2: _PIN1.14
A3: _PIN1.13
A4: _PIN1.12
A5: IC1.2 (B), _PIN1.11
A6: IC1.3 (C), _PIN1.10
A7: IC1.4 (G2A), _PIN1.9
A8: _PIN1.8
A9: _PIN1.7
A10: _PIN1.6
A11: _PIN1.5
A12: _PIN1.4
A13: _PIN1.3
A14: _PIN1.2
A15: _PIN1.1
BAUDCLK: IC3.8 (QD), U1.17 (RRC), U1.40 (TRC)
CLK: _PIN1.21
D0: U1.12 (RBR1), U1.19 (DR), U1.26 (TBR1), _PIN1.27
D1: U1.11 (RBR2), U1.22 (TBRE), U1.27 (TBR2), _PIN1.28
D2: U1.10 (RBR3), U1.28 (TBR3), _PIN1.29
D3: U1.9 (RBR4), U1.29 (TBR4), _PIN1.30
D4: U1.8 (RBR5), U1.30 (TBR5), _PIN1.31
D5: U1.7 (RBR6), U1.31 (TBR6), _PIN1.32
D6: U1.6 (RBR7), U1.32 (TBR7), _PIN1.33
D7: U1.5 (RBR8), U1.33 (TBR8), _PIN1.34
GND: 1.1, C1.2, C2.2, C3.2, C5.2, C7.2, IC1.8 (GND), IC2.7 (GND), IC3.6 (R0(1)), IC3.7 (R0(2)), IC3.10 (GND), QG1.7 (GND), U1.3 (GND), U1.21 (MR), U1.36 (SBS), U1.39 (EPE), _PIN1.17
unnamed: IC3.14 (CKA), QG1.8 (OUT)
unnamed: IC3.1 (CKB), IC3.12 (QA)
P00: IC1.15 (Y0)
P01: IC1.14 (Y1)
P20: IC1.13 (Y2)
P21: IC1.12 (Y3)
P40: IC1.11 (Y4), IC2.1 (I0), IC2.4 (I0)
P41: IC1.10 (Y5), IC2.9 (I0)
P60: IC1.9 (Y6)
P61: IC1.7 (Y7)
RX: R1.1, U1.20 (RRI)
RXX: 1.4, R1.2
TX: R2.1, U1.25 (TRO)
TXX: 1.5, R2.2
VCC: C1.1, C2.1, C3.1, C5.1, C7.1, IC1.16 (VCC), IC2.14 (VCC), IC3.5 (VCC), QG1.14 (VCC), U1.1 (VCC), U1.34 (CRL), U1.35 (PI), U1.37 (CLS2), U1.38 (CLS1), _PIN1.18

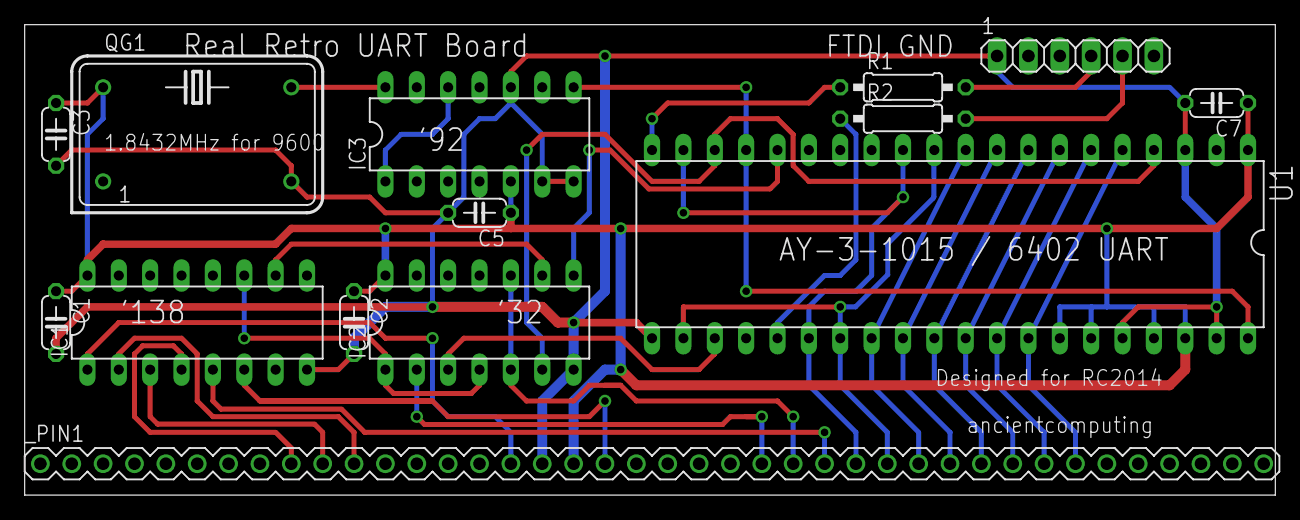
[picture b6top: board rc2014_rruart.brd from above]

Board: 2 copper layers, 101.3 x 38.1 mm, 14 parts (0 on the bottom side), 30 nets.
